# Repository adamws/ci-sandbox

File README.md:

## 0_sixty/0_sixty

[layout](0_sixty-kle.json) - [PCB](0_sixty.kicad_pcb)

[Open in keyboard-layout-editor](http://www.keyboard-layout-editor.com/##@@_c=#aaaaaa;&=0,0&_c=#cccccc;&=0,1&=0,2&=0,3&=0,4&=0,5&=0,6&=0,7&=0,8&=0,9&=0,10&_c=#aaaaaa;&=0,11;&@=1,0&_c=#cccccc;&=1,1&=1,2&=1,3&=1,4&=1,5&=1,6&=1,7&=1,8&=1,9&=1,10&_c=#aaaaaa;&=1,11;&@=2,0&_c=#cccccc;&=2,1&=2,2&=2,3&=2,4&=2,5&=2,6&=2,7&=2,8&=2,9&=2,10&_c=#aaaaaa;&=2,11;&@=3,0&_c=#cccccc;&=3,1&=3,2&=3,3&=3,4&=3,5&=3,6&=3,7&=3,8&=3,9&=3,10&_c=#aaaaaa;&=3,11;&@=4,0&=4,1&=4,2&=4,3&=4,4%0A%0A%0A0,0&=4,5%0A%0A%0A0,0&=4,6%0A%0A%0A0,0&=4,7%0A%0A%0A0,0&=4,8&=4,9&=4,10&=4,11;&@_x:4;&=4,4%0A%0A%0A0,1&_w:2;&=4,6%0A%0A%0A0,1&=4,7%0A%0A%0A0,1;&@_x:4&w:2;&=4,5%0A%0A%0A0,2&_w:2;&=4,6%0A%0A%0A0,2;&@_x:4;&=4,4%0A%0A%0A0,3&=4,5%0A%0A%0A0,3&_w:2;&=4,6%0A%0A%0A0,3;&@_x:4&w:2;&=4,5%0A%0A%0A0,4&=4,6%0A%0A%0A0,4&=4,7%0A%0A%0A0,4)

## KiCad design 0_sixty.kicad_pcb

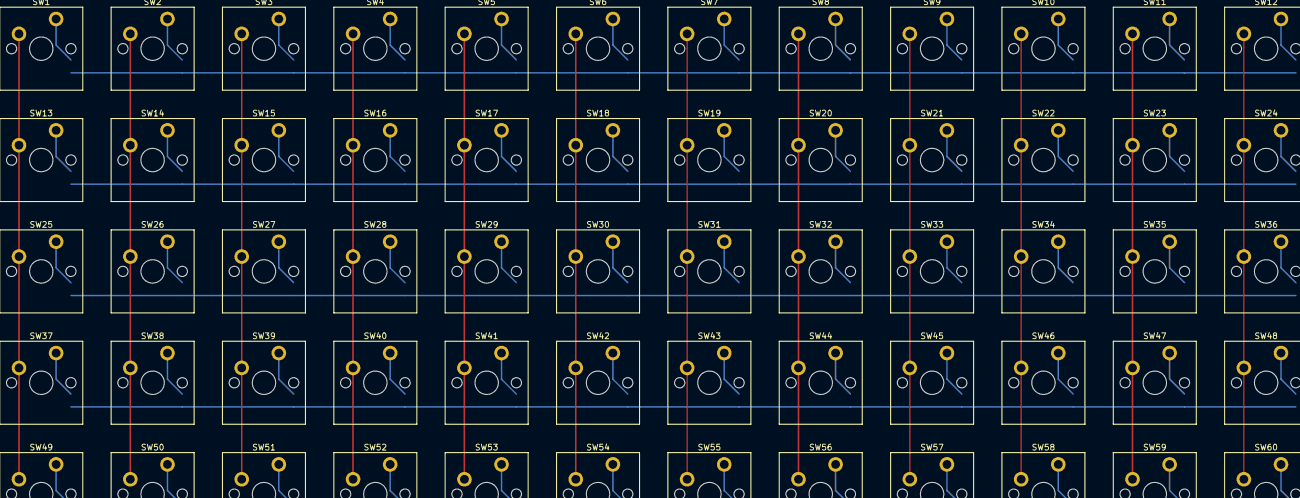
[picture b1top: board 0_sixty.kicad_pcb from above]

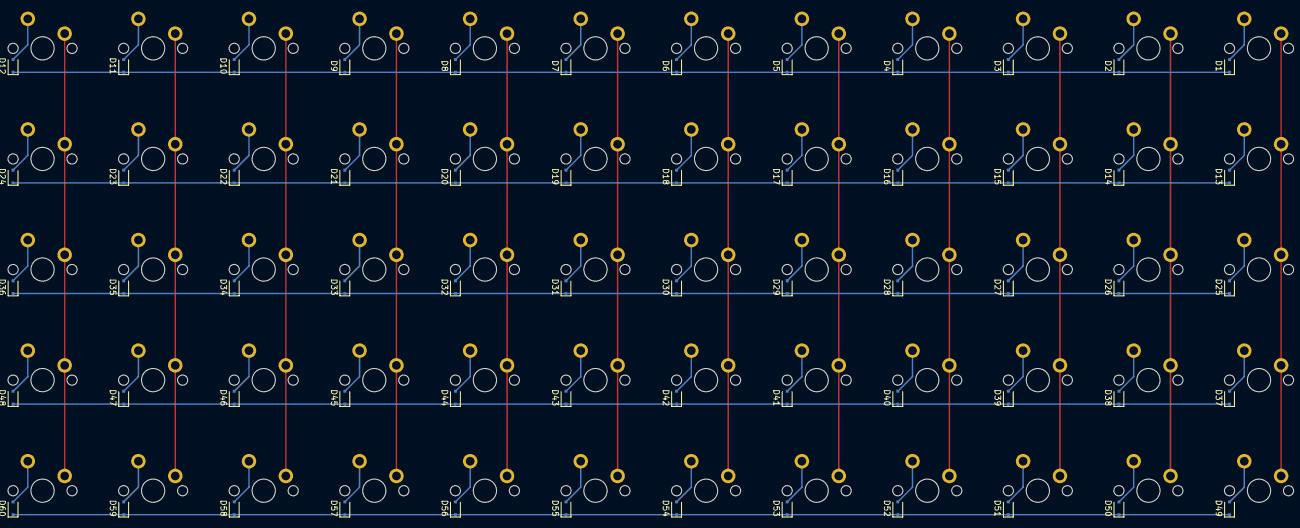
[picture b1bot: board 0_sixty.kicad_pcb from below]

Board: 2 copper layers, 120 parts (60 on the bottom side), 77 nets.

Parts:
D1, D2, D3, D4, D5, D6, D7, D8, D9, D10, D11, D12, D13, D14, D15, D16, D17, D18, D19, D20, D21, D22, D23, D24, D25, D26, D27, D28, D29, D30, D31, D32, D33, D34, D35, D36, D37, D38, D39, D40, D41, D42, D43, D44, D45, D46, D47, D48, D49, D50, D51, D52, D53, D54, D55, D56, D57, D58, D59, D60: D_SOD-323F
SW1, SW2, SW3, SW4, SW5, SW6, SW7, SW8, SW9, SW10, SW11, SW12, SW13, SW14, SW15, SW16, SW17, SW18, SW19, SW20, SW21, SW22, SW23, SW24, SW25, SW26, SW27, SW28, SW29, SW30, SW31, SW32, SW33, SW34, SW35, SW36, SW37, SW38, SW39, SW40, SW41, SW42, SW43, SW44, SW45, SW46, SW47, SW48, SW49, SW50, SW51, SW52, SW53, SW54, SW55, SW56, SW57, SW58, SW59, SW60: SW_Cherry_MX_PCB_1.00u

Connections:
COL0: SW1.1, SW13.1, SW25.1, SW37.1, SW49.1
COL1: SW2.1, SW14.1, SW26.1, SW38.1, SW50.1
COL2: SW3.1, SW15.1, SW27.1, SW39.1, SW51.1
COL3: SW4.1, SW16.1, SW28.1, SW40.1, SW52.1
COL4: SW5.1, SW17.1, SW29.1, SW41.1, SW53.1
COL5: SW6.1, SW18.1, SW30.1, SW42.1, SW54.1
COL6: SW7.1, SW19.1, SW31.1, SW43.1, SW55.1
COL7: SW8.1, SW20.1, SW32.1, SW44.1, SW56.1
COL8: SW9.1, SW21.1, SW33.1, SW45.1, SW57.1
COL9: SW10.1, SW22.1, SW34.1, SW46.1, SW58.1
COL10: SW11.1, SW23.1, SW35.1, SW47.1, SW59.1
COL11: SW12.1, SW24.1, SW36.1, SW48.1, SW60.1
unnamed: D1.2, SW1.2
unnamed: D2.2, SW2.2
unnamed: D3.2, SW3.2
unnamed: D4.2, SW4.2
unnamed: D5.2, SW5.2
unnamed: D6.2, SW6.2
unnamed: D7.2, SW7.2
unnamed: D8.2, SW8.2
unnamed: D9.2, SW9.2
unnamed: D10.2, SW10.2
unnamed: D11.2, SW11.2
unnamed: D12.2, SW12.2
unnamed: D13.2, SW13.2
unnamed: D14.2, SW14.2
unnamed: D15.2, SW15.2
unnamed: D16.2, SW16.2
unnamed: D17.2, SW17.2
unnamed: D18.2, SW18.2
unnamed: D19.2, SW19.2
unnamed: D20.2, SW20.2
unnamed: D21.2, SW21.2
unnamed: D22.2, SW22.2
unnamed: D23.2, SW23.2
unnamed: D24.2, SW24.2
unnamed: D25.2, SW25.2
unnamed: D26.2, SW26.2
unnamed: D27.2, SW27.2
unnamed: D28.2, SW28.2
unnamed: D29.2, SW29.2
unnamed: D30.2, SW30.2
unnamed: D31.2, SW31.2
unnamed: D32.2, SW32.2
unnamed: D33.2, SW33.2
unnamed: D34.2, SW34.2
unnamed: D35.2, SW35.2
unnamed: D36.2, SW36.2
unnamed: D37.2, SW37.2
unnamed: D38.2, SW38.2
unnamed: D39.2, SW39.2
unnamed: D40.2, SW40.2
unnamed: D41.2, SW41.2
unnamed: D42.2, SW42.2
unnamed: D43.2, SW43.2
unnamed: D44.2, SW44.2
unnamed: D45.2, SW45.2
unnamed: D46.2, SW46.2
unnamed: D47.2, SW47.2
unnamed: D48.2, SW48.2
unnamed: D49.2, SW49.2
unnamed: D50.2, SW50.2
unnamed: D51.2, SW51.2
unnamed: D52.2, SW52.2
unnamed: D53.2, SW53.2
unnamed: D54.2, SW54.2
unnamed: D55.2, SW55.2
unnamed: D56.2, SW56.2
unnamed: D57.2, SW57.2
unnamed: D58.2, SW58.2
unnamed: D59.2, SW59.2
unnamed: D60.2, SW60.2
ROW0: D1.1, D2.1, D3.1, D4.1, D5.1, D6.1, D7.1, D8.1, D9.1, D10.1, D11.1, D12.1
ROW1: D13.1, D14.1, D15.1, D16.1, D17.1, D18.1, D19.1, D20.1, D21.1, D22.1, D23.1, D24.1
ROW2: D25.1, D26.1, D27.1, D28.1, D29.1, D30.1, D31.1, D32.1, D33.1, D34.1, D35.1, D36.1
ROW3: D37.1, D38.1, D39.1, D40.1, D41.1, D42.1, D43.1, D44.1, D45.1, D46.1, D47.1, D48.1
ROW4: D49.1, D50.1, D51.1, D52.1, D53.1, D54.1, D55.1, D56.1, D57.1, D58.1, D59.1, D60.1

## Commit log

2023-01-26 path filtering
2023-01-26 trigger job
2023-01-26 should not trigger
2023-01-26 should trigger
2023-01-26 is filters allowed here?
2023-01-26 continuation selection
2023-01-26 what will happen with both on master?
2023-01-26 trigger
2023-01-26 fix?
2023-01-26 would that work?
2023-01-26 testing
2023-01-26 progress
2023-01-27 test syntax
2023-01-27 testing conditions
2023-01-27 env pass between steps?
2023-02-19 testing windows
2023-02-19 scoop
2023-02-19 kicad
2023-02-20 python env
2023-02-20 bash
2023-02-20 test
2023-02-20 test scoop cache
2023-02-20 path
2023-02-20 powershell
2023-02-20 works?
2023-02-20 download
2023-03-02 testing vuepress in dir
2023-03-02 change basepath
2023-03-02 testing docs deployment
2023-03-06 Deploy documentation: a05c27972327c21f2ba8a85bbb96627b8b728996
2023-03-21 add second job to have two statuses
2023-03-22 waiter
2023-03-22 ignore fail?
2023-03-22 status patching
2023-03-22 refactor
2023-04-17 temp host
2023-06-20 Add kicad-kbplacer.zip
2023-06-21 test kicad pcm
2023-09-12 Experiment with github releases
2023-10-02 Testing how it will render
2023-12-09 automatic releases testing
2023-12-09 add filter
2023-12-09 repo name change
2023-12-09 test2
2024-04-17 purge
2024-04-17 conan test
2024-04-17 Test on branch
2024-04-17 test my another branch
2024-04-18 test another branch
2024-04-18 try on macos
